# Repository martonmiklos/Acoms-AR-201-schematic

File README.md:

# Acoms-AR-201-schematic
Reverse engineered schematics of the Acoms AR-201 2CH AM receiver

As of now only the BEC part completed.

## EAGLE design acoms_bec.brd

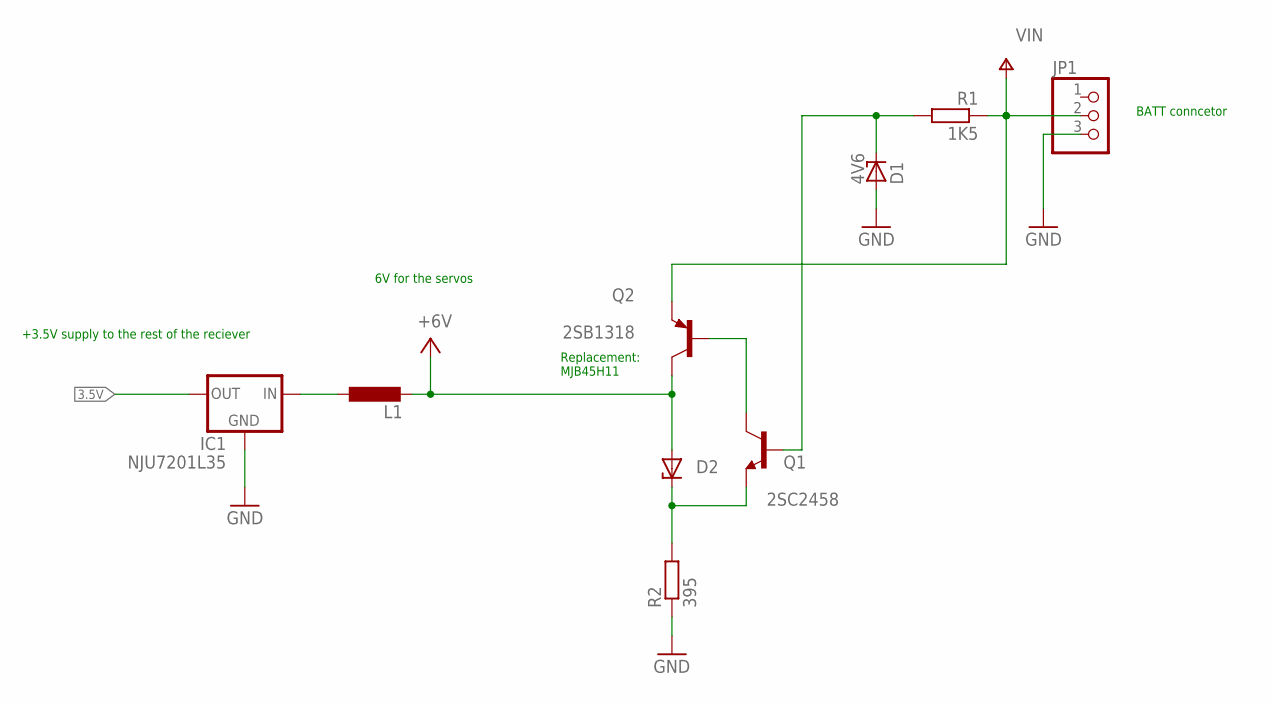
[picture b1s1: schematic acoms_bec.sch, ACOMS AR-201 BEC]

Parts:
D1: 4V6; ZDIO-2.5
D2: ZENER-DIODEZD-2.5; ZDIO-2.5
IC1: NJU7201L35; TO-92
JP1: PINHD-1X3; 1X03
L1: L-EU0207/2V; 0207/2V
Q1: 2SC2458; TO-92
Q2: 2SB1318; TO-92
R1: 1K5; 0309V
R2: 395; 0309V

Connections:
3.5V: IC1.3 (OUT)
+6V: D2.A, L1.2, Q2.2 (C)
GND: D1.A, IC1.1 (GND), JP1.3, R2.1
unnamed: IC1.2 (IN), L1.1
unnamed: Q1.2 (C), Q2.3 (B)
unnamed: D2.C, Q1.1 (E), R2.2
unnamed: D1.C, Q1.3 (B), R1.2
V+: JP1.2, Q2.1 (E), R1.1

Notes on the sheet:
+3.5V supply to the rest of the reciever
6V for the servos
BATT conncetor
Replacement: MJB45H11

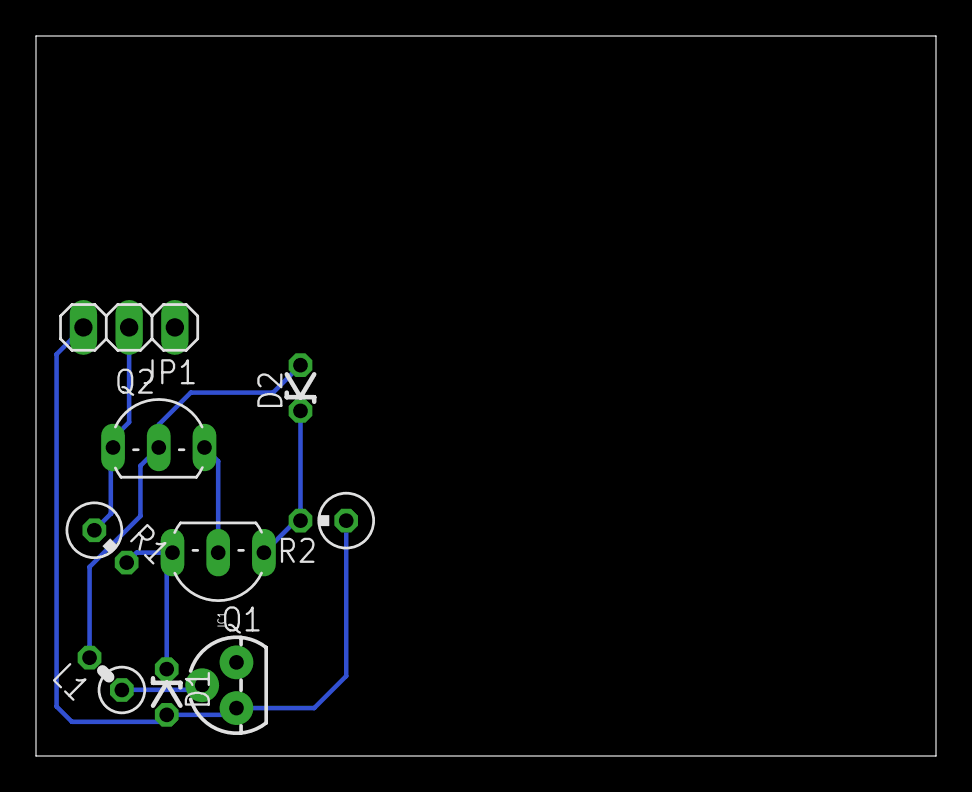
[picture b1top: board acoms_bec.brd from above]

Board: 2 copper layers, 50.0 x 40.0 mm, 9 parts (0 on the bottom side), 7 nets.

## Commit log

2019-03-24 repo init
2019-03-24 add image
2019-03-25 Transistor name update to the original

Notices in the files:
parts and their libraries:
SparkFun: Licensing: CC v3.0 Share-Alike You are welcome to use this library for commercial purposes.
